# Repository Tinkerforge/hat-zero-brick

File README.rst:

HAT Zero Brick
==============

This repository contains the firmware source code and the hardware design
files. The documentation generator configs can be found at
https://github.com/Tinkerforge/generators

Repository Content
------------------

software/:
 * examples/: Examples for all supported languages
 * build/: Compiled files
 * src/: Source code of firmware
 * Makefile: Makefile to build project

hardware/:
 * Contains KiCad project files and additionally schematics as PDF

datasheets/:
 * Contains datasheets for sensors and complex ICs that are used

Hardware
--------

The hardware is designed with the open source EDA Suite KiCad
(http://www.kicad.org). Before you are able to open the files,
you have to install the Tinkerforge kicad-libraries
(https://github.com/Tinkerforge/kicad-libraries). You can either clone
them directly in hardware/ or clone them in a separate folder and
symlink them into hardware/
(ln -s kicad_path/kicad-libraries project_path/hardware). After that you
can open the .pro file in hardware/ with KiCad and from there view and
modify the schematics and the PCB layout.

Software
--------

If you want to do your own Brick/Bricklet firmware development we highly
recommend that you use our build environment setup script and read the
tutorial (https://www.tinkerforge.com/en/doc/Tutorials/Tutorial_Build_Environment/Tutorial.html).

To compile the C code we recommend you to install the newest GNU Arm Embedded
Toolchain (https://launchpad.net/gcc-arm-embedded/+download).
You also need to install bricklib2 (https://github.com/Tinkerforge/bricklib2).

You can either clone it directly in software/src/ or clone it in a
separate folder and symlink it into software/src/
(ln -s bricklib_path/bricklib2 project_path/software/src/). Finally make sure to
have CMake installed (http://www.cmake.org/cmake/resources/software.html).

After that you can build the firmware by invoking make in software/.
The firmware (.zbin) can then be found in software/build/ and uploaded
with brickv (click button "Flashing" on start screen).

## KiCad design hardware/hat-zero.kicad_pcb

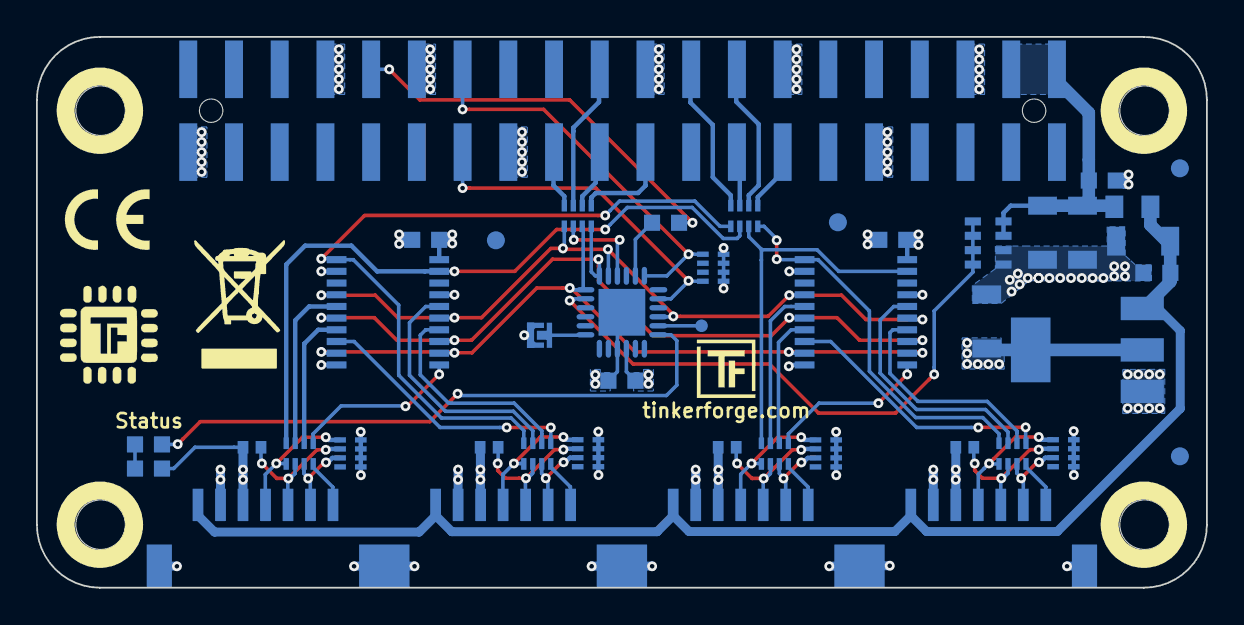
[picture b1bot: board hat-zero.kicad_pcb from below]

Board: 4 copper layers, 65.0 x 30.6 mm, 46 parts (42 on the bottom side), 57 nets.

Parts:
C101, C104, C106, C201, C202: 100nF; C0603F
C102, C103, C105, C107: 10uF; C1206
CP201, CP202, CP203, CP204: 220pF; 4X0402
D101: blue; D0603F
Fiducial_Mark: VAL**; Fiducial_Mark
Fiducial_Mark#2, Fiducial_Mark#3, Fiducial_Mark#4: VAL**; Fiducial_Mark
J101: Boot; SolderJumper
J102: Raspberry_Pi_Zero; raspberrypi_zero_hat
L101: FB; R0805
P101: Debug; DEBUG_PAD
P201, P202, P203, P204: CON-SENSOR2
R1, R2, R3, R4: 100k; R0402F
R101, R102: 1k; R0603F
RP102: 10k; 4X0603
RP103: 3.9k; 4X0402
RP104, RP106, RP201, RP202, RP203, RP204: 82; 4X0402
U101: XMC1100; QFN24-4x4mm-0.5mm
U102: LD1117; SOT-223
U201, U202: 74AHC244; TSSOP20
VAL: CE_5mm
VAL#2: WEEE_7mm

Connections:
+5V: C102.1, C105.2, C106.2, J102.2, J102.4, L101.2, RP102.5, RP102.6
B-3V3: C101.1, C107.1, C201.2, C202.2, D101.1, P201.3, P202.3, P203.3, P204.3, R1.1, R2.1, R3.1, R4.1, RP103.1, RP103.2, RP103.3, RP103.4, U101.10, U102.2, U201.20, U202.20
B-5V: C103.1, C104.1, L101.1, P201.1, P202.1, P203.1, P204.1, U102.3
B-CLK: RP106.1, U101.15, U101.23, U201.4, U201.15, U202.4, U202.15
B-CS0: RP104.4, RP201.8, U201.1
B-CS1: RP104.3, RP202.8, U201.19
B-CS2: RP104.1, RP203.8, U202.1
B-CS3: RP104.2, RP204.8, U202.19
B-CS4: RP106.2, U101.22
B-MISO: RP106.3, U101.1, U201.9, U201.12, U202.9, U202.12
B-MOSI: RP106.4, U101.24, U201.6, U201.13, U202.6, U202.13
GND: C101.2, C102.2, C103.2, C104.2, C105.1, C106.1, C107.2, C201.1, C202.1, CP201.5, CP201.6, CP201.7, CP201.8, CP202.5, CP202.6, CP202.7, CP202.8, CP203.5, CP203.6, CP203.7, CP203.8, CP204.5, CP204.6, CP204.7, CP204.8, J101.1, J102.6, J102.9, J102.14, J102.20, J102.25, J102.30, J102.34, J102.39, P201.2, P201.EP, P202.2, P202.EP, P203.2, P203.EP, P204.2, P204.EP, RP102.7, RP102.8, U101.9, U101.EXP, U102.1, U201.2, U201.10, U201.17, U202.2, U202.10, U202.17
IN-VOLTAGE: RP102.1, RP102.2, RP102.3, RP102.4, U101.2
unnamed: CP201.1, P201.4, RP201.1
unnamed: CP201.2, P201.5, R1.2, RP201.2
unnamed: CP201.3, P201.6, RP201.3
unnamed: CP202.1, P202.4, RP202.1
unnamed: CP202.2, P202.5, R2.2, RP202.2
unnamed: CP202.3, P202.6, RP202.3
unnamed: CP203.1, P203.4, RP203.1
unnamed: CP203.2, P203.5, R3.2, RP203.2
unnamed: CP203.3, P203.6, RP203.3
unnamed: CP204.1, P204.4, RP204.1
unnamed: CP204.2, P204.5, R4.2, RP204.2
unnamed: CP204.3, P204.6, RP204.3
unnamed: D101.2, R102.1
unnamed: J101.2, U101.6
unnamed: J102.13, RP104.5
unnamed: J102.15, RP104.7
unnamed: J102.16, RP104.6
unnamed: J102.18, RP104.8
unnamed: J102.19, RP106.5
unnamed: J102.21, RP106.6
unnamed: J102.22, RP106.7
unnamed: J102.23, RP106.8
unnamed: J102.32, R101.2
unnamed: P101.1, U101.14
unnamed: P201.7, RP201.4
unnamed: P202.7, RP202.4
unnamed: P203.7, RP203.4
unnamed: P204.7, RP204.4
unnamed: R102.2, U101.13
unnamed: RP201.5, U201.8
unnamed: RP201.6, U201.14
unnamed: RP201.7, U201.16
unnamed: RP202.5, U201.11
unnamed: RP202.6, U201.7
unnamed: RP202.7, U201.5
unnamed: RP203.5, U202.8
unnamed: RP203.6, U202.14
unnamed: RP203.7, U202.16
unnamed: RP204.5, U202.11
unnamed: RP204.6, U202.7
unnamed: RP204.7, U202.5
RASP-GP: R101.1, U101.20
RASP-SC: J102.28, RP103.5, U101.19
RASP-SD: J102.27, RP103.8, U101.17

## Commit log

2018-08-09 initial files check in
2018-08-09 Rename Bricklet
2018-08-10 prototype of hat zero bricklet added
2018-08-24 add sym table and pcb hint
2018-09-03 Add auto-generated stub implementation
2018-09-03 Add RPi eeprom device-tree files
2018-09-03 Add EEPROM implementation
2018-09-03 Add USB voltage implementation
2018-09-03 Update .gitignore with generated device-tree files
2018-09-04 fix graphical elements
2019-02-07 add hint
2019-03-19 changed pcb layout to single sided placement, added clock pullup's, changed symlib-table
2019-03-25 add logo
2019-04-03 ordered data
2019-04-03 Update eeprom data
2019-04-03 Update led/boot pins
2019-04-03 Add get_usb_voltage API
2019-04-05 Recategorize HAT Zero as Brick
2019-04-05 Use Brick device id (starts with 1)
2019-04-29 Bricklet -> Brick in product string
2019-04-30 Turn logging off
2019-07-01 add schematic, fix descriptions
2019-07-01 add 3d data
2019-07-02 Add auto-generated examples
2019-07-03 examples: Format rust example.
2019-07-11 Update changelog and readme
2019-09-12 Add USB voltage callback
2019-09-12 Add ref for 2.0.1
2020-01-13 examples: Use python3 input instead of python2 raw_input.
2020-08-19 Add uc examples.
2020-08-25 uc: Fix whitespace
2020-08-27 uc: Fix warnings.
2020-09-02 uc: Add example driver note.
2020-10-16 uc: Fix divisor type.
2021-10-25 Update KiCad link
    https://www.kicad.org/blog/2021/10/Avoid-links-to-former-kicad-domain/
2022-04-19 examples: uc: Rename TF_HalContext to TF_HAL.
2022-04-27 uc: Adapt to bindings changes
2022-07-06 Add license files.
2023-11-21 Add support for Raspberry Pi 5.
    See https://github.com/Tinkerforge/hat-brick/commit/e4480c7a
2023-11-27 Increase version number
2023-11-27 Update changelog
2025-10-04 Fix compatibility with new Docker build image (GCC 14.2.1)
